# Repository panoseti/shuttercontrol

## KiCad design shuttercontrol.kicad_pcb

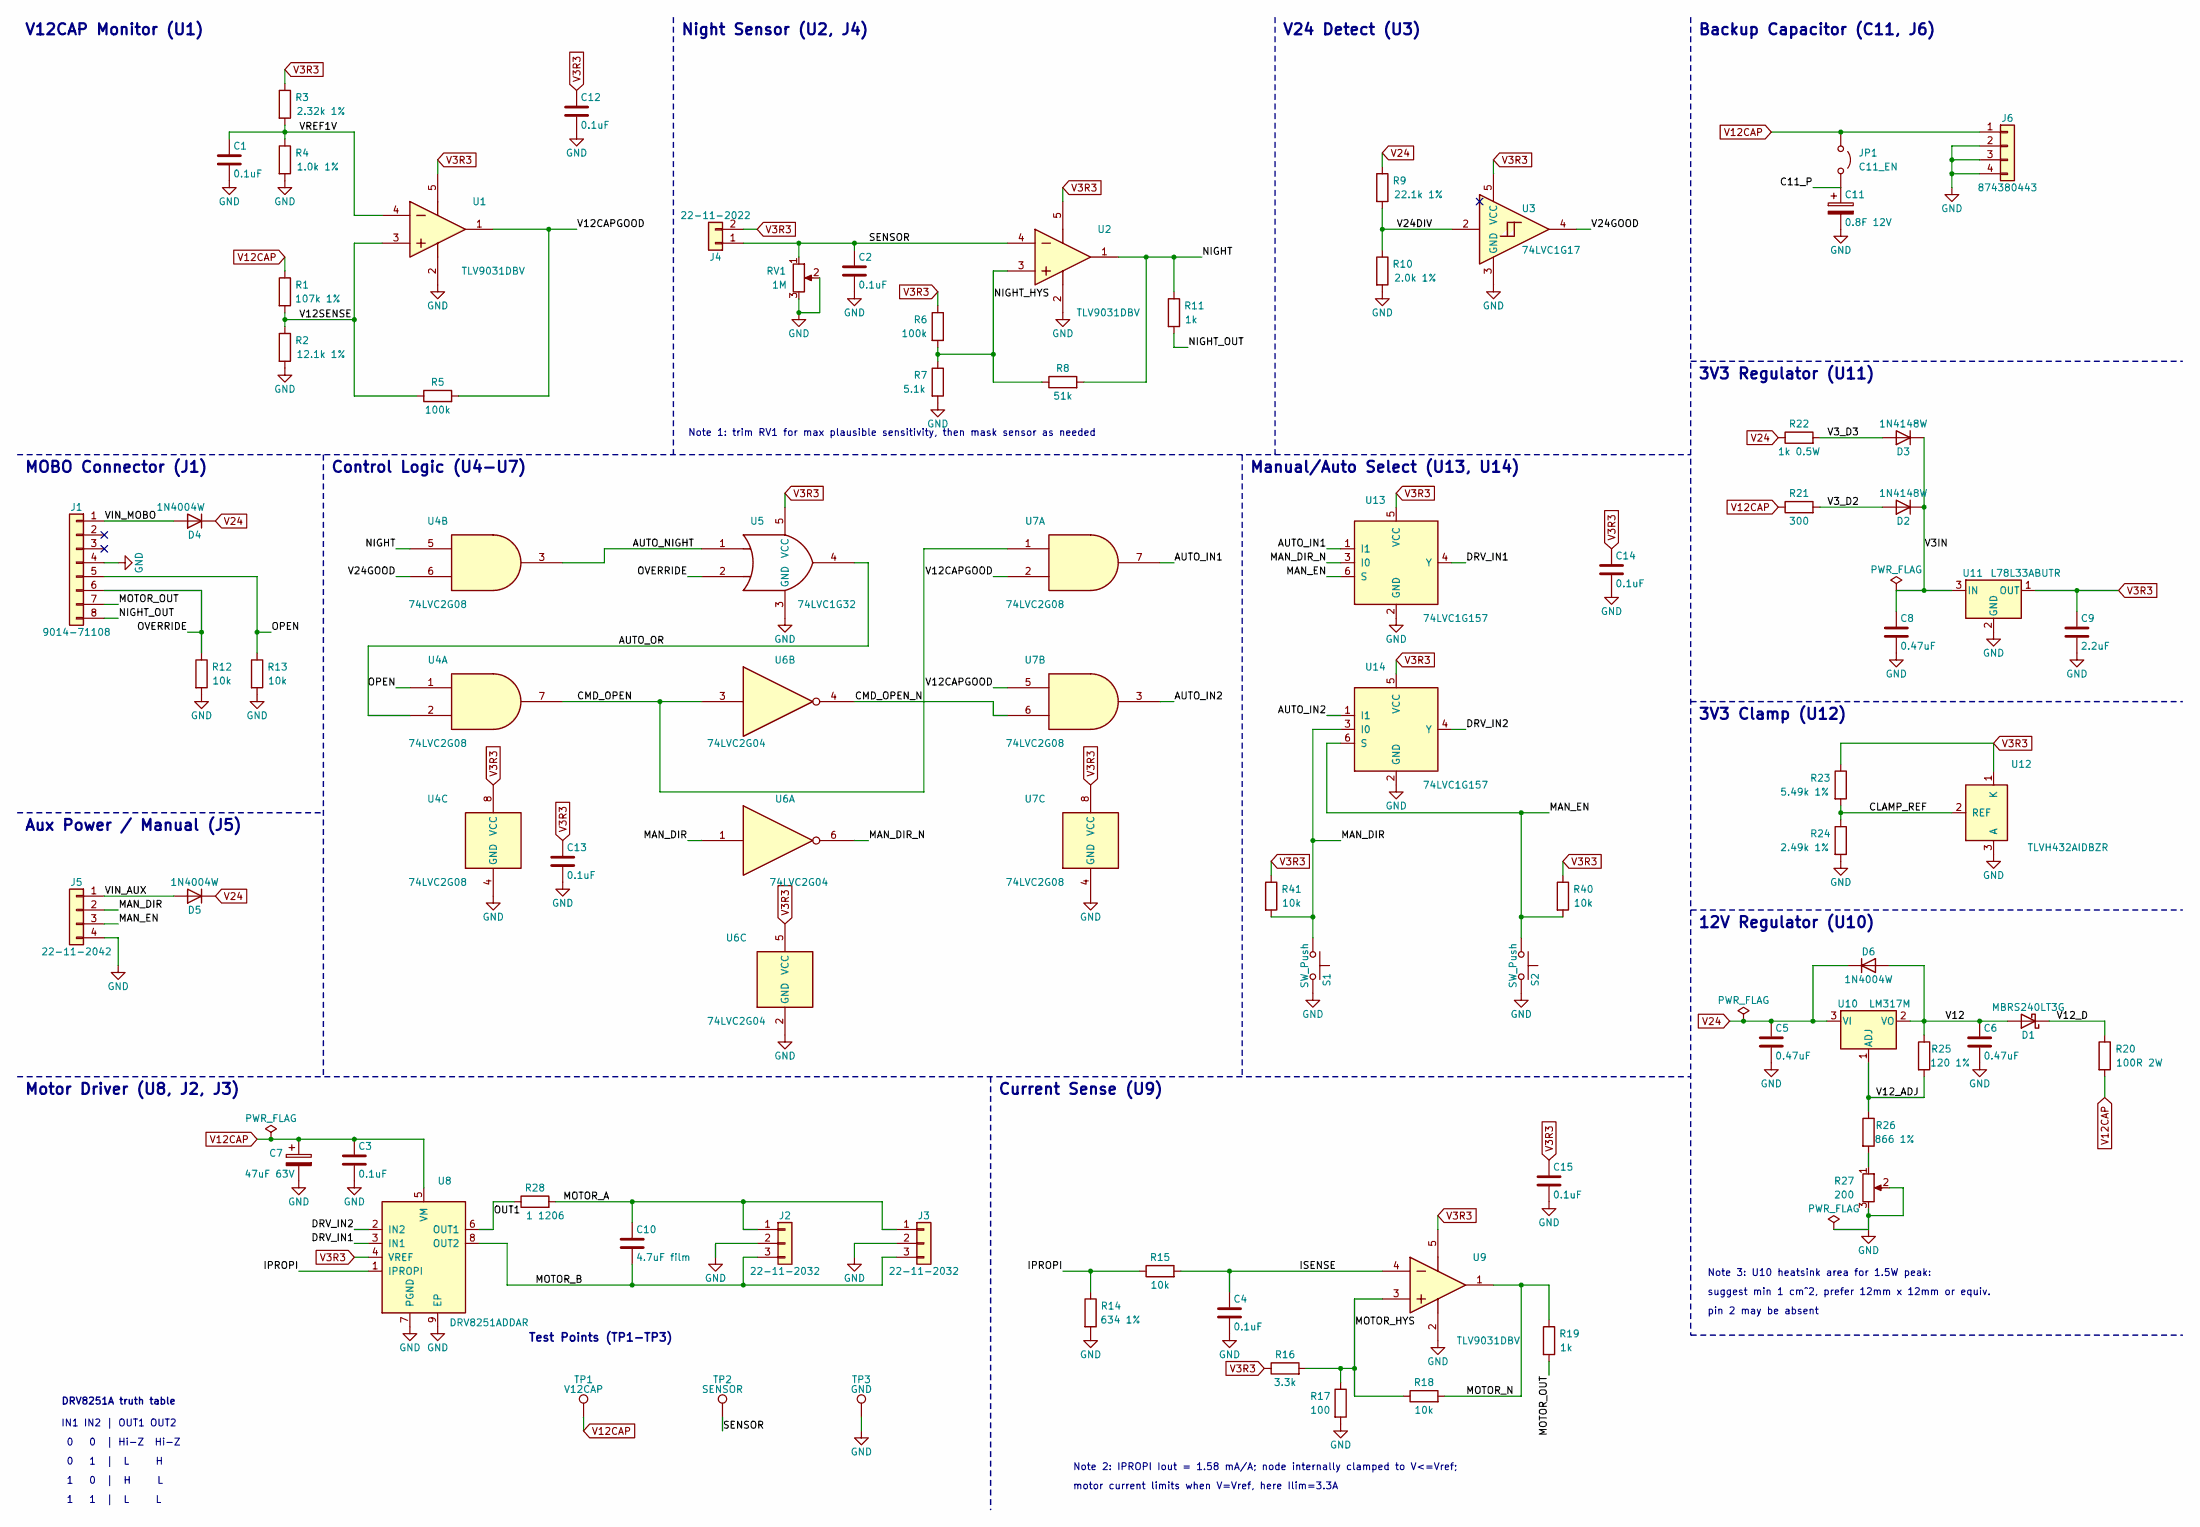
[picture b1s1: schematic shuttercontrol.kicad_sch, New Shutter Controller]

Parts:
C1, C2, C3, C4, C12, C13, C14, C15: 0.1uF; C_0805_2012Metric; LCSC C49678
C5, C6, C8: 0.47uF; C_0805_2012Metric; LCSC C13967
C7: 47uF 63V; CP_Radial_D8.0mm_P3.50mm; MPN UBT1J470MPD8TD
C9: 2.2uF; C_0805_2012Metric; LCSC C377773
C10: 4.7uF film; C_Rect_L7.2mm_W11.0mm_P5.00mm_FKS2_FKP2_MKS2_MKP2; MPN B32529D5475M289
C11: 0.8F 12V; CDA_CPM_DA_D17.0-21.0mm_P8.50-10.50mm; MPN CPM-12R0L804R-TW
D1: MBRS240LT3G; D_SMB; MPN MBRS240LT3G; LCSC C8165
D2, D3: 1N4148W; D_SOD-123; MPN 1N4148W; LCSC C117823
D4, D5, D6: 1N4004W; D_SOD-123F; MPN 1N4004W; LCSC C18199087
J1: 9014-71108; PinSocket_1x08_P2.54mm_Vertical; MPN 90147-1108; LCSC C6032581
J2, J3: 22-11-2032; Molex_KK-254_AE-6410-03A_1x03_P2.54mm_Vertical; MPN 22112032; LCSC C505163
J4: 22-11-2022; Molex_KK-254_AE-6410-02A_1x02_P2.54mm_Vertical; MPN 22112022; LCSC C505162
J5: 22-11-2042; Molex_KK-254_AE-6410-04A_1x04_P2.54mm_Vertical; MPN 22112042; LCSC C114123
J6: 874380443; Molex_Pico-SPOX_87438-0443_1x04_P1.50mm_Horizontal; MPN 874380443; LCSC C564208
JP1: C11_EN; PinHeader_1x02_P2.54mm_Vertical; MPN PZ254V-11-02P; LCSC C492401
R1: 107k 1%; R_0805_2012Metric; LCSC C276295
R2: 12.1k 1%; R_0805_2012Metric; LCSC C17431
R3: 2.32k 1%; R_0805_2012Metric; LCSC C2933374
R4: 1.0k 1%; R_0805_2012Metric; LCSC C17513
R5, R6: 100k; R_0805_2012Metric; LCSC C149504
R7: 5.1k; R_0805_2012Metric; LCSC C27834
R8: 51k; R_0805_2012Metric; LCSC C17737
R9: 22.1k 1%; R_0805_2012Metric; LCSC C17552
R10: 2.0k 1%; R_0805_2012Metric; LCSC C17604
R11, R19: 1k; R_0805_2012Metric; LCSC C17513
R12, R13, R15, R18, R40, R41: 10k; R_0805_2012Metric; LCSC C17414
R14: 634 1%; R_0805_2012Metric; LCSC C17787
R16: 3.3k; R_0805_2012Metric; LCSC C26010
R17: 100; R_0805_2012Metric; LCSC C17408
R20: 100R 2W; R_Axial_DIN0617_L17.0mm_D6.0mm_P20.32mm_Horizontal; LCSC C58717
R21: 300; R_0805_2012Metric; LCSC C17617
R22: 1k 0.5W; R_1210_3225Metric; LCSC C2930439
R23: 5.49k 1%; R_0805_2012Metric; LCSC C2933466
R24: 2.49k 1%; R_0805_2012Metric; LCSC C21237
R25: 120 1%; R_0805_2012Metric; LCSC C17437
R26: 866 1%; R_0805_2012Metric; LCSC C17849
R27: 200; Potentiometer_Bourns_3314G_Vertical; MPN 3314G-1-201E; LCSC C52238
R28: 1 1206; R_1206_3216Metric; MPN 1206W4F100KT5E; LCSC C17928
RV1: 1M; Potentiometer_Bourns_3314G_Vertical; MPN 3314G-1-105E; LCSC C780218
S1, S2: SW_Push; SW_SPST_TL3342; LCSC C2886897
TP1: V12CAP; TestPoint_Keystone_5000_Red_Miniature; MPN 5000; Digikey 36-5000-ND
TP2: SENSOR; TestPoint_Keystone_5002_White_Miniature; MPN 5002; Digikey 36-5002-ND
TP3: GND; TestPoint_Keystone_5001_Black_Miniature; MPN 5001; Digikey 36-5001-ND
U1, U2, U9: TLV9031DBV; SOT-23-5; MPN TLV9031DBV; LCSC C29777121
U3: 74LVC1G17; SOT-23-5; MPN 74LVC1G17DBV; LCSC C7836
U4, U7: 74LVC2G08; VSSOP-8_2.3x2mm_P0.5mm; MPN 74LVC2G08DCT; LCSC C456135
U5: 74LVC1G32; SOT-23-5; MPN 74LVC1G32DBV; LCSC C10096
U6: 74LVC2G04; SOT-23-6; MPN 74LVC2G04DBV; LCSC C10428
U8: DRV8251ADDAR; HSOP-8-1EP_3.9x4.9mm_P1.27mm_EP2.41x3.1mm; MPN DRV8251ADDAR; LCSC C5218844
U10: LM317M; TO-252-2; MPN LM317MABDTRKG; LCSC C427699
U11: L78L33ABUTR; SOT-89-3_RectPads; MPN L78L33ABUTR; LCSC C81362
U12: TLVH432AIDBZR; SOT-23-3; MPN TLVH432AIDBZR; LCSC C2157628
U13, U14: 74LVC1G157; SOT-363_SC-70-6; MPN 74LVC1G157GW,125; LCSC C135822

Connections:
/AUTO_IN1: U7.7, U13.1 (I1)
/AUTO_IN2: U7.3, U14.1 (I1)
/AUTO_NIGHT: U4.3, U5.1
/AUTO_OR: U4.2, U5.4
/C11_P: C11.1, JP1.2 (B)
/CLAMP_REF: R23.2, R24.1, U12.2 (REF)
/CMD_OPEN: U4.7, U6.3, U7.1
/CMD_OPEN_N: U6.4, U7.6
/DRV_IN1: U8.3 (IN1), U13.4 (Y)
/DRV_IN2: U8.2 (IN2), U14.4 (Y)
/IPROPI: R14.1, R15.1, U8.1 (IPROPI)
/ISENSE: C4.1, R15.2, U9.4 (-IN)
/MAN_DIR: J5.2, R41.2, S1.1, U6.1, U14.3 (I0)
/MAN_DIR_N: U6.6, U13.3 (I0)
/MAN_EN: J5.3, R40.2, S2.1, U13.6 (S), U14.6 (S)
/MOTOR_A: C10.1, J2.1, J3.1, R28.2
/MOTOR_B: C10.2, J2.3, J3.3, U8.8 (OUT2)
/MOTOR_HYS: R16.2, R17.1, R18.1, U9.3 (+IN)
/MOTOR_N: R18.2, R19.1, U9.1 (OUT)
/MOTOR_OUT: J1.7, R19.2
/NIGHT: R8.2, R11.1, U2.1 (OUT), U4.5
/NIGHT_HYS: R6.2, R7.1, R8.1, U2.3 (+IN)
/NIGHT_OUT: J1.8, R11.2
/OPEN: J1.5, R13.1, U4.1
/OUT1: R28.1, U8.6 (OUT1)
/OVERRIDE: J1.6, R12.1, U5.2
/SENSOR: C2.1, J4.1, RV1.1, TP2.1 (1_1), U2.4 (-IN)
/V3IN: C8.1, D2.1 (K), D3.1 (K), U11.3 (IN)
/V3_D2: D2.2 (A), R21.2
/V3_D3: D3.2 (A), R22.2
/V12: C6.1, D1.2 (A), D6.2 (A), R25.1, U10.2 (VO)
/V12CAPGOOD: R5.2, U1.1 (OUT), U7.2, U7.5
/V12SENSE: R1.2, R2.1, R5.1, U1.3 (+IN)
/V12_ADJ: R25.2, R26.1, U10.1 (ADJ)
/V12_D: D1.1 (K), R20.1
/V24DIV: R9.2, R10.1, U3.2
/V24GOOD: U3.4, U4.6
/VIN_AUX: D5.2 (A), J5.1
/VIN_MOBO: D4.2 (A), J1.1
/VREF1V: C1.1, R3.2, R4.1, U1.4 (-IN)
GND: C1.2, C2.2, C3.2, C4.2, C5.2, C6.2, C7.2, C8.2, C9.2, C11.2, C12.2, C13.2, C14.2, C15.2, J1.4, J2.2, J3.2, J5.4, J6.2, J6.3, J6.4, R2.2, R4.2, R7.2, R10.2, R12.2, R13.2, R14.2, R17.2, R24.2, R27.2, R27.3, RV1.2, RV1.3, S1.2, S2.2, TP3.1 (1_1), U1.2 (V-), U2.2 (V-), U3.3 (GND), U4.4 (GND), U5.3 (GND), U6.2 (GND), U7.4 (GND), U8.7 (PGND), U8.9 (EP), U9.2 (V-), U11.2 (GND), U12.3 (A), U13.2 (GND), U14.2 (GND)
unnamed: R26.2, R27.1
V3R3: C9.1, C12.1, C13.1, C14.1, C15.1, J4.2, R3.1, R6.1, R16.1, R23.1, R40.1, R41.1, U1.5 (V+), U2.5 (V+), U3.5 (VCC), U4.8 (VCC), U5.5 (VCC), U6.5 (VCC), U7.8 (VCC), U8.4 (VREF), U9.5 (V+), U11.1 (OUT), U12.1 (K), U13.5 (VCC), U14.5 (VCC)
V12CAP: C3.1, C7.1, J6.1, JP1.1 (A), R1.1, R20.2, R21.1, TP1.1 (1_1), U8.5 (VM)
V24: C5.1, D4.1 (K), D5.1 (K), D6.1 (K), R9.1, R22.1, U10.3 (VI)

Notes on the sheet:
DRV8251A truth table
3V3 Regulator (U11)
Manual/Auto Select (U13, U14)
Note 2: IPROPI Iout = 1.58 mA/A; node internally clamped to V<=Vref;
Test Points (TP1-TP3)
V12CAP Monitor (U1)
Note 1: trim RV1 for max plausible sensitivity, then mask sensor as needed
Current Sense (U9)
1 0 | H L
pin 2 may be absent
motor current limits when V=Vref, here Ilim=3.3A
Motor Driver (U8, J2, J3)
Backup Capacitor (C11, J6)
0 0 | Hi-Z Hi-Z
3V3 Clamp (U12)
Control Logic (U4-U7)
Note 3: U10 heatsink area for 1.5W peak:
12V Regulator (U10)
V24 Detect (U3)
0 1 | L H
1 1 | L L
Aux Power / Manual (J5)
Night Sensor (U2, J4)
suggest min 1 cm^2, prefer 12mm x 12mm or equiv.
MOBO Connector (J1)
IN1 IN2 | OUT1 OUT2

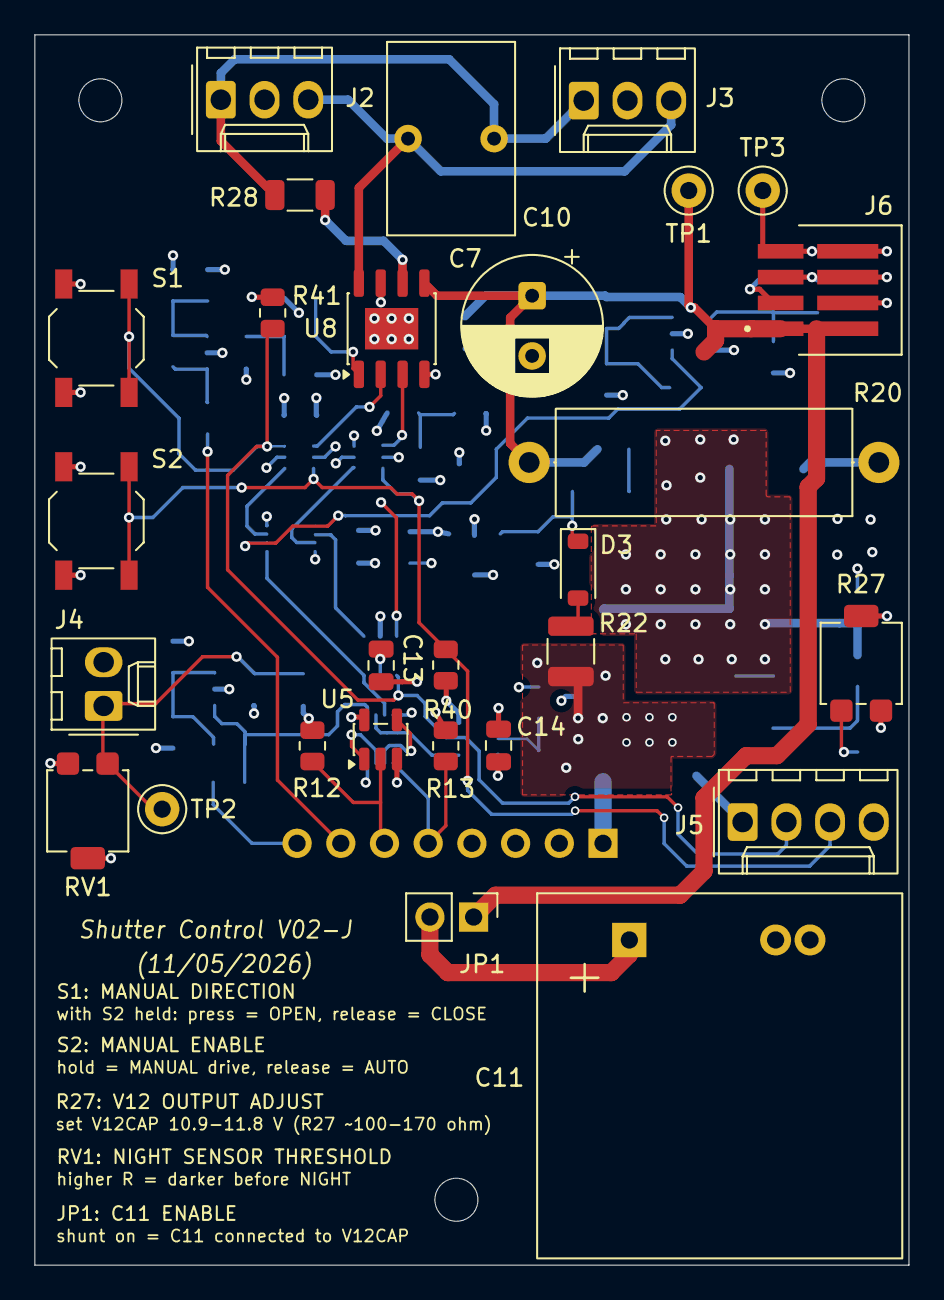
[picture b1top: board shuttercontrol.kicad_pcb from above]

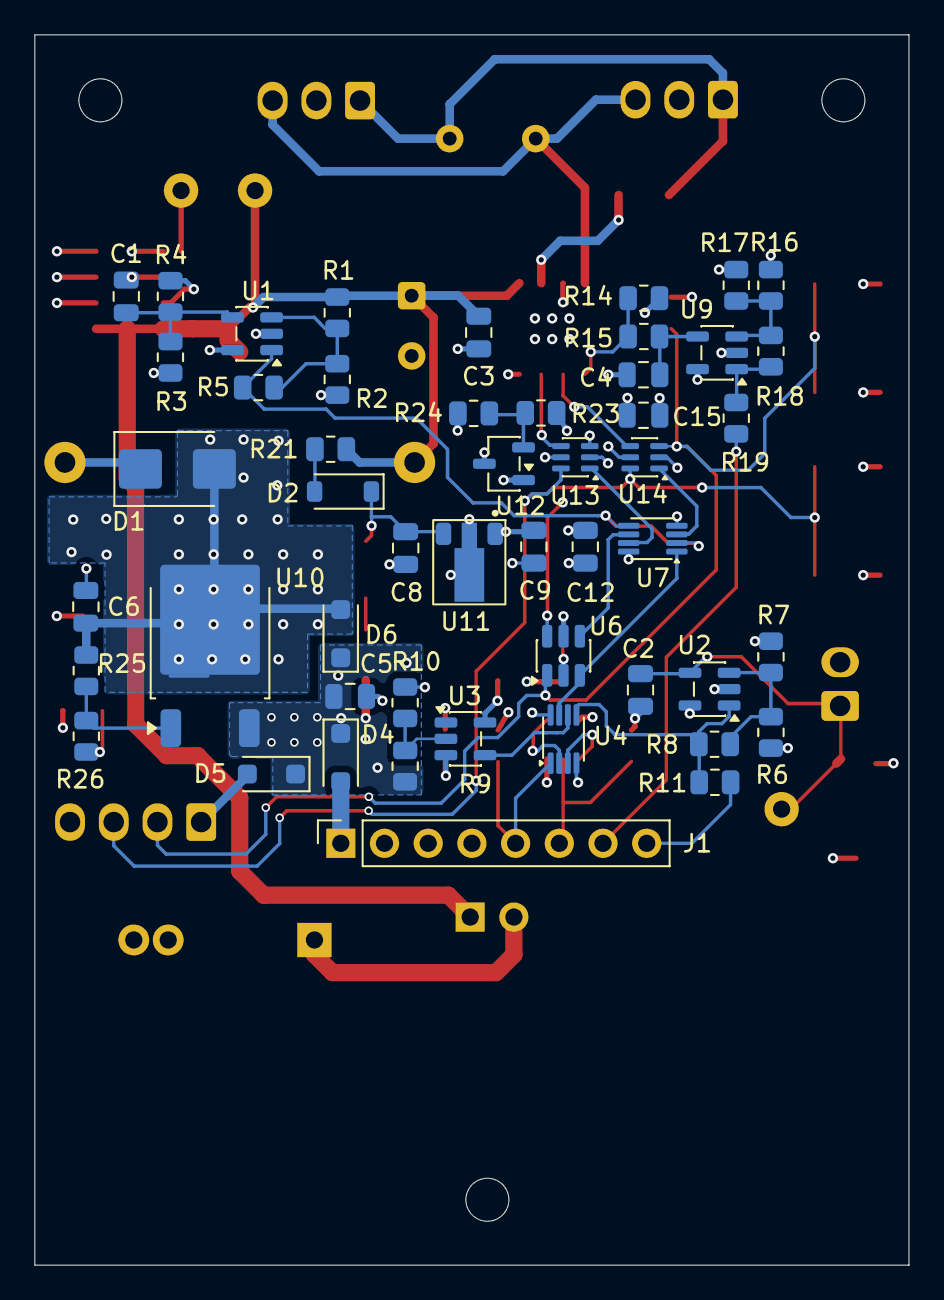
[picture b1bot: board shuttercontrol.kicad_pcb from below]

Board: 4 copper layers, 50.8 x 71.5 mm, 81 parts (50 on the bottom side), 45 nets.

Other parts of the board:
H1, H2, H3: MountingHole_2.5mm

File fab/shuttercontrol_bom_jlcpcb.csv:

Comment,Designator,Footprint,JLCPCB Part #
0.1uF,"C1,C2,C3,C4,C12,C13,C14,C15",C_0805_2012Metric,C49678
0.47uF,"C5,C6,C8",C_0805_2012Metric,C13967
2.2uF,C9,C_0805_2012Metric,C377773
MBRS240LT3G,D1,D_SMB,C8165
1N4148W,"D2,D3",D_SOD-123,C117823
1N4004W,"D4,D5,D6",D_SOD-123F,C18199087
9014-71108,J1,PinSocket_1x08_P2.54mm_Vertical,C6032581
22-11-2032,"J2,J3",Molex_KK-254_AE-6410-03A_1x03_P2.54mm_Vertical,C505163
22-11-2022,J4,Molex_KK-254_AE-6410-02A_1x02_P2.54mm_Vertical,C505162
22-11-2042,J5,Molex_KK-254_AE-6410-04A_1x04_P2.54mm_Vertical,C114123
874380443,J6,Molex_Pico-SPOX_87438-0443_1x04_P1.50mm_Horizontal,C564208
C11_EN,JP1,PinHeader_1x02_P2.54mm_Vertical,C492401
107k 1%,R1,R_0805_2012Metric,C276295
12.1k 1%,R2,R_0805_2012Metric,C17431
2.32k 1%,R3,R_0805_2012Metric,C2933374
1.0k 1%,"R4,R11,R19",R_0805_2012Metric,C17513
100k,"R5,R6",R_0805_2012Metric,C149504
5.1k,R7,R_0805_2012Metric,C27834
51k,R8,R_0805_2012Metric,C17737
22.1k 1%,R9,R_0805_2012Metric,C17552
2.0k 1%,R10,R_0805_2012Metric,C17604
10k,"R12,R13,R15,R18,R40,R41",R_0805_2012Metric,C17414
634 1%,R14,R_0805_2012Metric,C17787
3.3k,R16,R_0805_2012Metric,C26010
100,R17,R_0805_2012Metric,C17408
100R 2W,R20,R_Axial_DIN0617_L17.0mm_D6.0mm_P20.32mm_Horizontal,C58717
300,R21,R_0805_2012Metric,C17617
1k 0.5W,R22,R_1210_3225Metric,C2930439
5.49k 1%,R23,R_0805_2012Metric,C2933466
2.49k 1%,R24,R_0805_2012Metric,C21237
120 1%,R25,R_0805_2012Metric,C17437
866 1%,R26,R_0805_2012Metric,C17849
200,R27,Potentiometer_Bourns_3314G_Vertical,C52238
1 1206,R28,R_1206_3216Metric,C17928
1M,RV1,Potentiometer_Bourns_3314G_Vertical,C780218
SW_Push,"S1,S2",SW_SPST_TL3342,C2886897
TLV9031DBV,"U1,U2,U9",SOT-23-5,C29777121
74LVC1G17,U3,SOT-23-5,C7836
74LVC2G08,"U4,U7",VSSOP-8_2.3x2mm_P0.5mm,C456135
74LVC1G32,U5,SOT-23-5,C10096
74LVC2G04,U6,SOT-23-6,C10428
DRV8251ADDAR,U8,HSOP-8-1EP_3.9x4.9mm_P1.27mm_EP2.41x3.1mm,C5218844
LM317M,U10,TO-252-2,C427699
L78L33ABUTR,U11,SOT-89-3_RectPads,C81362
TLVH432AIDBZR,U12,SOT-23-3,C2157628
74LVC1G157,"U13,U14",SOT-363_SC-70-6,C135822
